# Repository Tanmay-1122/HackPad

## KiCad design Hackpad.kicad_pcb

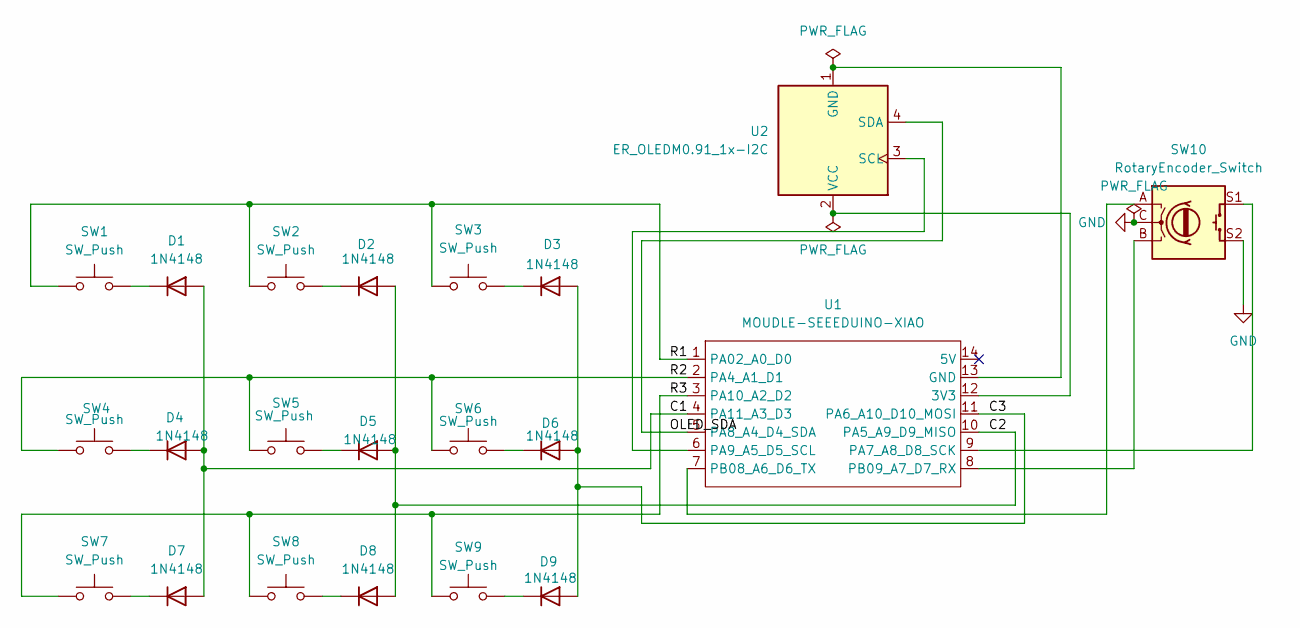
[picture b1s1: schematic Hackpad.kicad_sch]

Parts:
D1, D2, D3, D4, D5, D6, D7, D8, D9: 1N4148; D_DO-35_SOD27_P7.62mm_Horizontal
SW1, SW2, SW3, SW4, SW5, SW6, SW7, SW8, SW9: SW_Push; SW_Cherry_MX_1.00u_PCB
SW10: RotaryEncoder_Switch; RotaryEncoder_Alps_EC11E-Switch_Vertical_H20mm_CircularMoun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
U1: MOUDLE-SEEEDUINO-XIAO; XIAO-Generic-Hybrid-14P-2.54-21X17.8MM
U2: ER_OLEDM0.91_1x-I2C

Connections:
/C1: D1.2 (A), D4.2 (A), D7.2 (A), U1.4 (PA11_A3_D3)
/C2: D2.2 (A), D5.2 (A), D8.2 (A), U1.10 (PA5_A9_D9_MISO)
/C3: D3.2 (A), D6.2 (A), D9.2 (A), U1.11 (PA6_A10_D10_MOSI)
/OLED_SDA: U1.5 (PA8_A4_D4_SDA), U2.4 (SDA)
/R1: SW1.1, SW2.1, SW3.1, U1.1 (PA02_A0_D0)
/R2: SW4.1, SW5.1, SW6.1, U1.2 (PA4_A1_D1)
/R3: SW7.1, SW8.1, SW9.1, U1.3 (PA10_A2_D2)
GND: SW10.C, SW10.S2
unnamed: D1.1 (K), SW1.2
unnamed: D2.1 (K), SW2.2
unnamed: D3.1 (K), SW3.2
unnamed: D4.1 (K), SW4.2
unnamed: D5.1 (K), SW5.2
unnamed: D6.1 (K), SW6.2
unnamed: D7.1 (K), SW7.2
unnamed: D8.1 (K), SW8.2
unnamed: D9.1 (K), SW9.2
unnamed: U1.12 (3V3), U2.2 (VCC)
unnamed: U1.13 (GND), U2.1 (GND)
unnamed: SW10.S1, U1.9 (PA7_A8_D8_SCK)
unnamed: U1.6 (PA9_A5_D5_SCL), U2.3 (SCL)
unnamed: SW10.A, U1.7 (PB08_A6_D6_TX)
unnamed: SW10.B, U1.8 (PB09_A7_D7_RX)

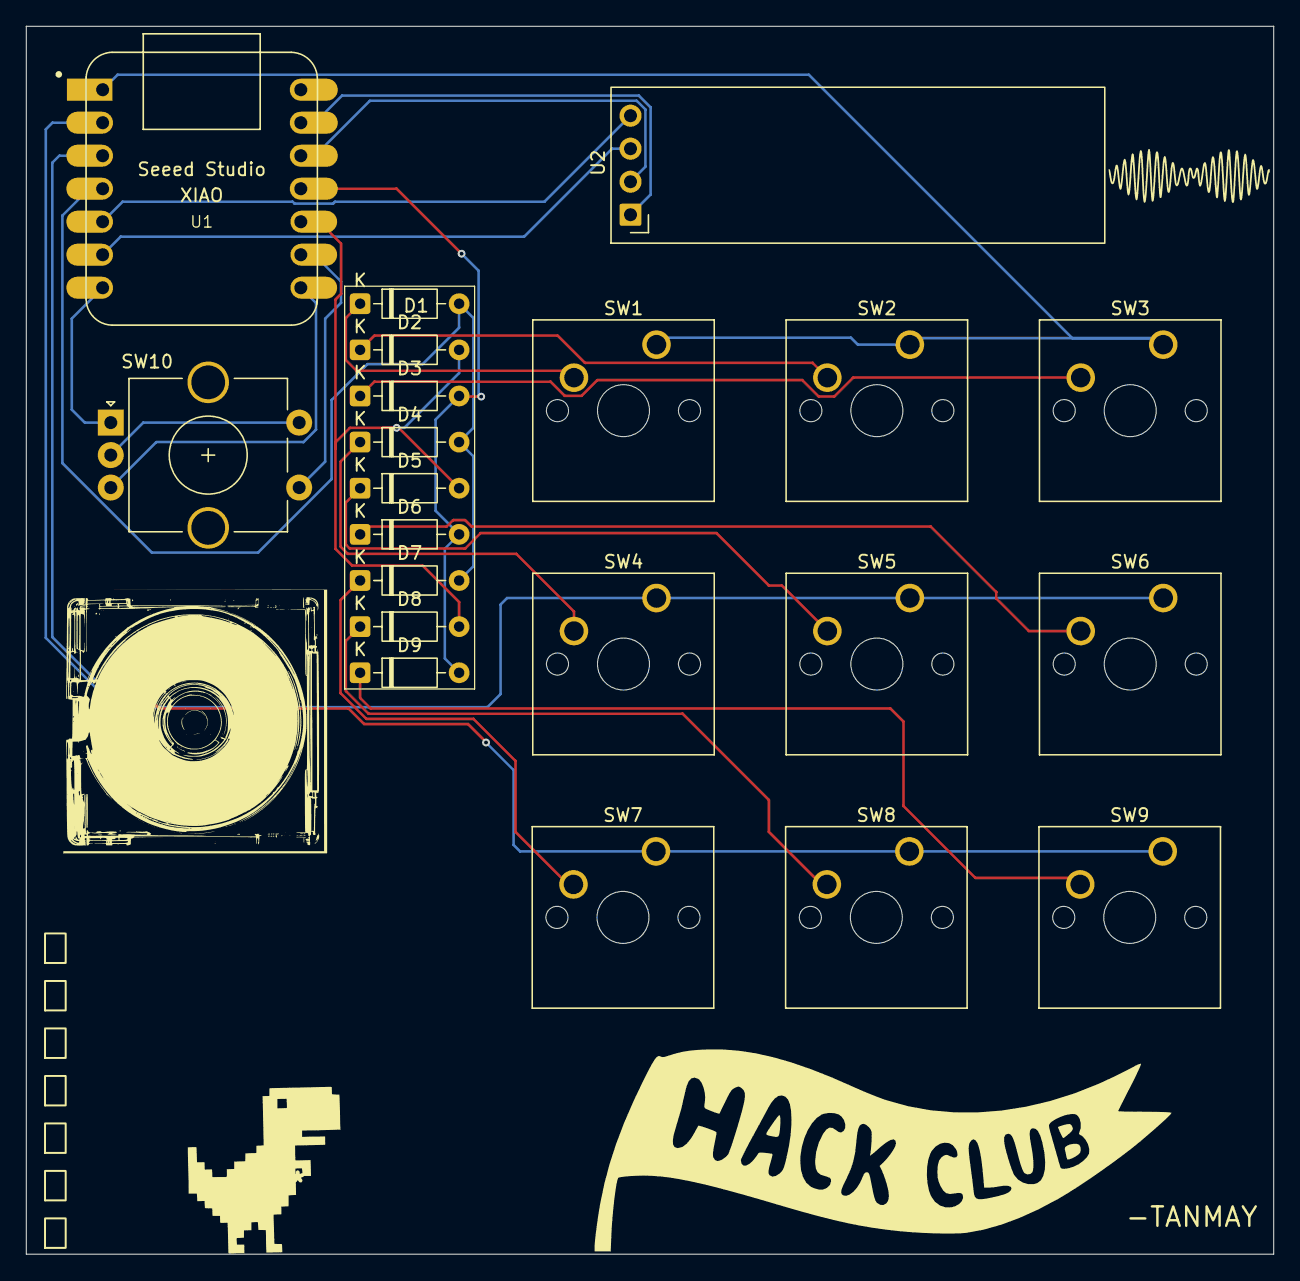
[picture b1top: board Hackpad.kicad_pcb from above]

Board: 2 copper layers, 96.0 x 94.5 mm, 21 parts (0 on the bottom side), 23 nets.

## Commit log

2026-06-21 Add KiCad project files
